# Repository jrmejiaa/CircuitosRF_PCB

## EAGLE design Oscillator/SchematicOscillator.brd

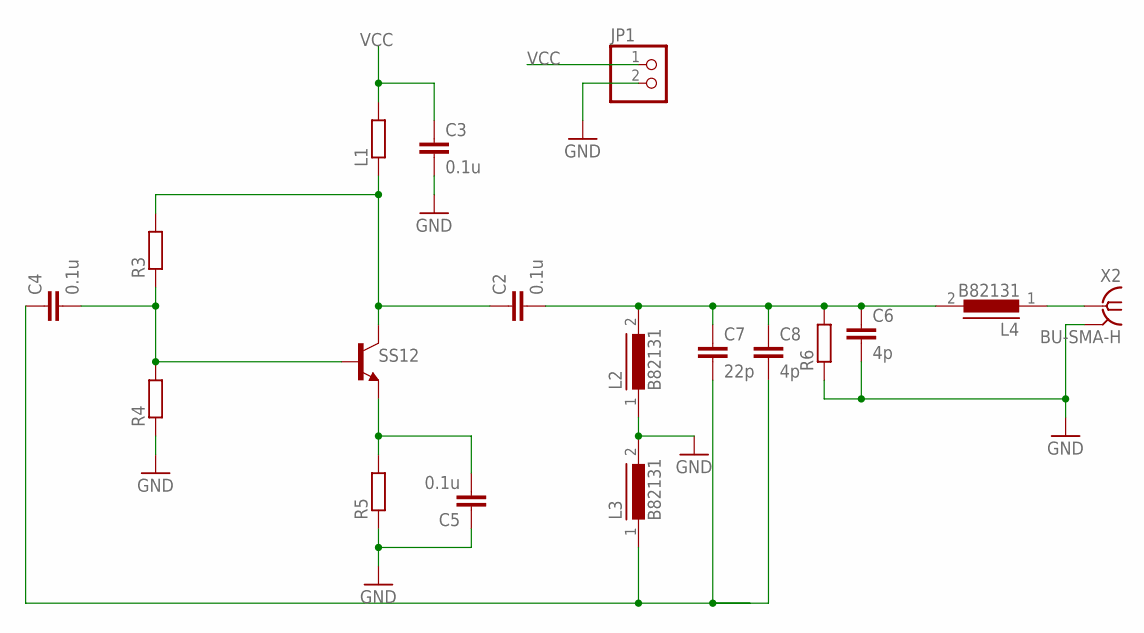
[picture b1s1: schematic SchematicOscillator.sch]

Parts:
C2, C3, C4, C5: 0.1u; C0805
C6, C8: 4p; C1206
C7: 22p; C0805
JP1: PINHD-1X2; 1X02
L1: R-EU_M0805; M0805
L2, L3, L4: B82131; SUKW1-17
R3, R4, R5, R6: R-EU_R1206; R1206
SS12: -NPN-TO92; TO92
X2: BU-SMA-H

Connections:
GND: C3.2, C5.1, C6.2, JP1.2, L2.1, L3.2, R4.1, R5.1, R6.1, X2.2, X2.3 (2), X2.4 (2), X2.5 (2)
unnamed: C2.1, L1.1, R3.2, SS12.3 (C)
unnamed: C5.2, R5.2, SS12.1 (E)
unnamed: C4.2, R3.1, R4.2, SS12.2 (B)
unnamed: L4.1, X2.1
unnamed: C2.2, C6.1, C7.1, C8.1, L2.2, L4.2, R6.2
unnamed: C4.1, C7.2, C8.2, L3.1
VCC: C3.1, JP1.1, L1.2

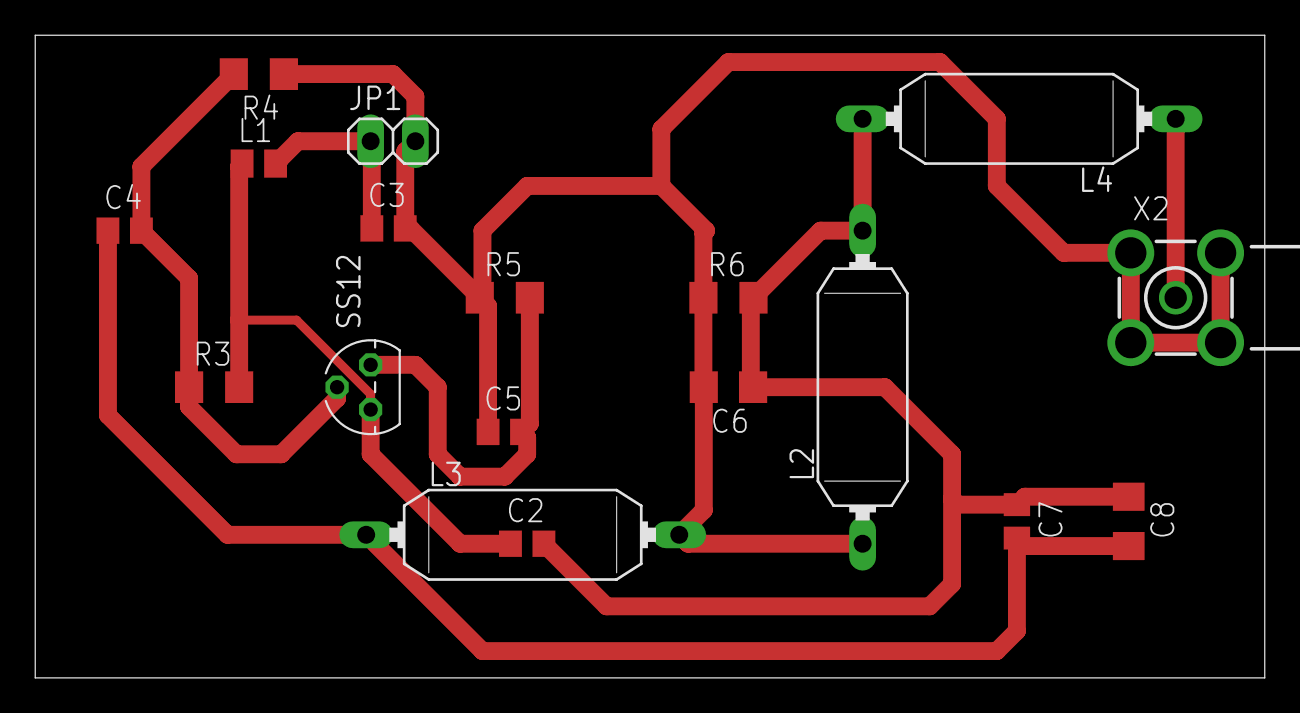
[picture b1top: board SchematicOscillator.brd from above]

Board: 2 copper layers, 69.8 x 36.5 mm, 18 parts (0 on the bottom side), 8 nets.

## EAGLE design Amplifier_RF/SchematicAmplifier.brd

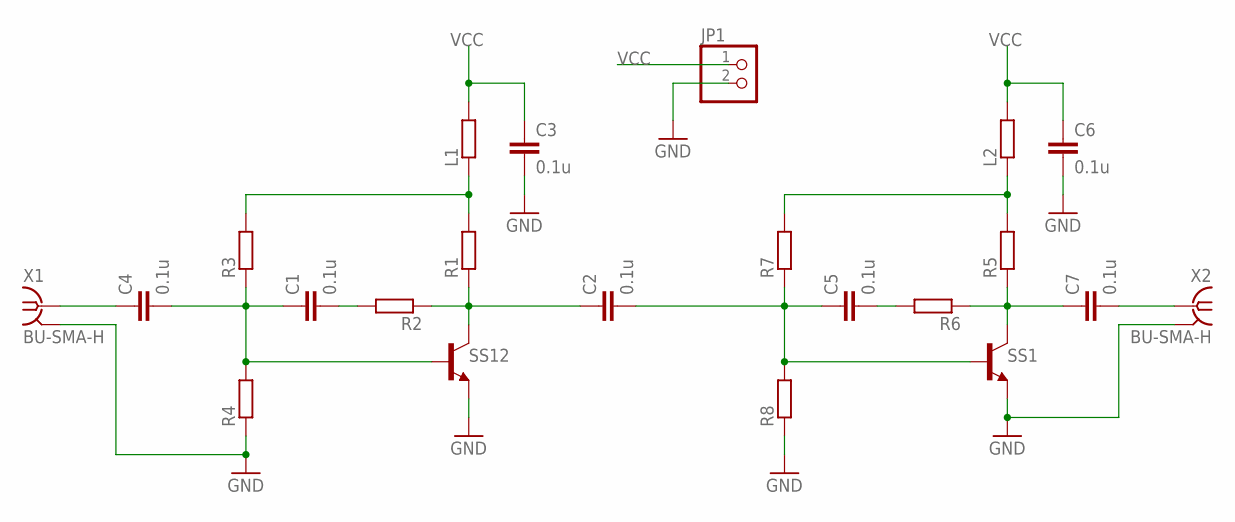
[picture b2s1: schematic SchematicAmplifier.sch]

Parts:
C1, C2, C3, C4, C5, C6, C7: 0.1u; C0805
JP1: PINHD-1X2; 1X02
L1, L2: R-EU_M0805; M0805
R1, R2, R3, R4, R5, R6, R7, R8: R-EU_R1206; R1206
SS1, SS12: -NPN-TO92; TO92
X1, X2: BU-SMA-H

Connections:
GND: C3.2, C6.2, JP1.2, R4.1, R8.1, SS1.1 (E), SS12.1 (E), X1.2, X1.3 (2), X1.4 (2), X1.5 (2), X2.2, X2.3 (2), X2.4 (2), X2.5 (2)
unnamed: C1.2, R2.2
unnamed: L1.1, R1.2, R3.2
unnamed: C2.1, R1.1, R2.1, SS12.3 (C)
unnamed: C4.1, X1.1
unnamed: C1.1, C4.2, R3.1, R4.2, SS12.2 (B)
unnamed: L2.1, R5.2, R7.2
unnamed: C7.1, R5.1, R6.1, SS1.3 (C)
unnamed: C2.2, C5.1, R7.1, R8.2, SS1.2 (B)
unnamed: C5.2, R6.2
unnamed: C7.2, X2.1
VCC: C3.1, C6.1, JP1.1, L1.2, L2.2

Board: 2 copper layers, 22 parts (0 on the bottom side), 12 nets, no tracks yet.

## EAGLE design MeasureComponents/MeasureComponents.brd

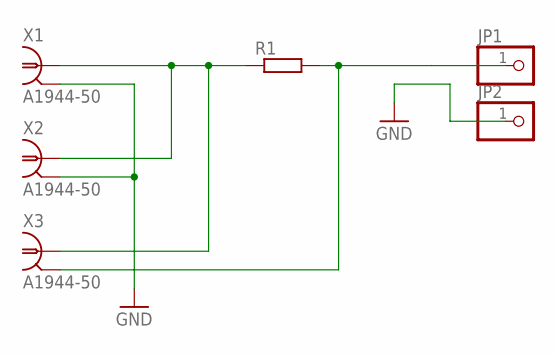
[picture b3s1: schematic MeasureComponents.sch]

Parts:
JP1, JP2: PINHD-1X1; 1X01
R1: R-EU_M1206; M1206
X1, X2, X3: A1944-50; A1944

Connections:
GND: JP2.1, X1.2, X1.3 (2), X1.4 (2), X1.5 (2), X2.2, X2.3 (2), X2.4 (2), X2.5 (2)
unnamed: R1.1, X1.1, X2.1, X3.1
unnamed: JP1.1, R1.2, X3.2, X3.3 (2), X3.4 (2), X3.5 (2)

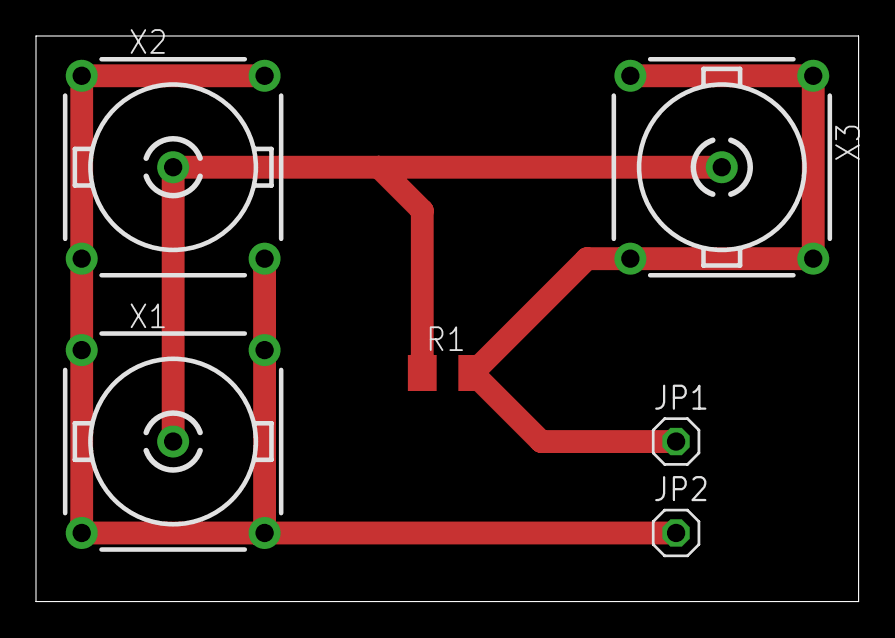
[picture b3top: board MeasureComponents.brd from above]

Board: 2 copper layers, 45.7 x 31.4 mm, 6 parts (0 on the bottom side), 3 nets.

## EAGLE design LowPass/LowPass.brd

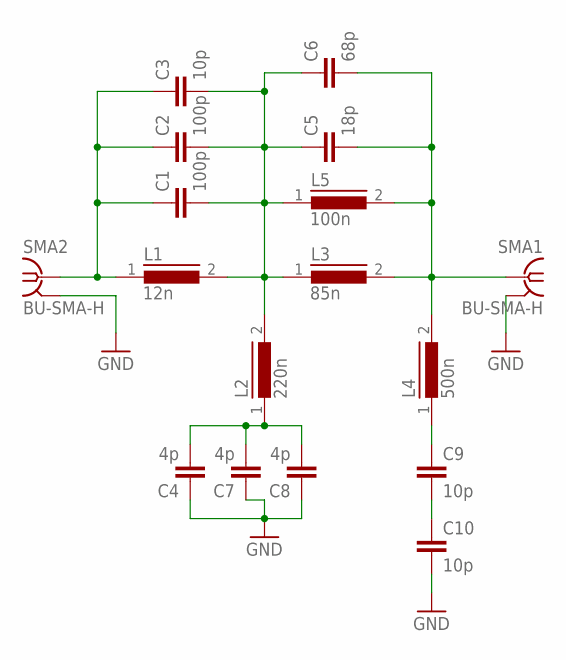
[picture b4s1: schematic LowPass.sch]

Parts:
C1, C2: 100p; C0805
C3, C9, C10: 10p; C0805
C4, C7, C8: 4p; C1206
C5: 18p; C0805
C6: 68p; C0402
L1: 12n; MICC10
L2: 220n; MICC10
L3: 85n; MICC10
L4: 500n; MICC10
L5: 100n; MICC10
SMA1, SMA2: BU-SMA-H

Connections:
GND: C4.1, C7.1, C8.1, C10.2, SMA1.2, SMA1.3 (2), SMA1.4 (2), SMA1.5 (2), SMA2.2, SMA2.3 (2), SMA2.4 (2), SMA2.5 (2)
unnamed: C1.1, C2.1, C3.1, L1.1, SMA2.1
unnamed: C1.2, C2.2, C3.2, C5.1, C6.1, L1.2, L2.2, L3.1, L5.1
unnamed: C5.2, C6.2, L3.2, L4.2, L5.2, SMA1.1
unnamed: C9.1, L4.1
unnamed: C9.2, C10.1
unnamed: C4.2, C7.2, C8.2, L2.1

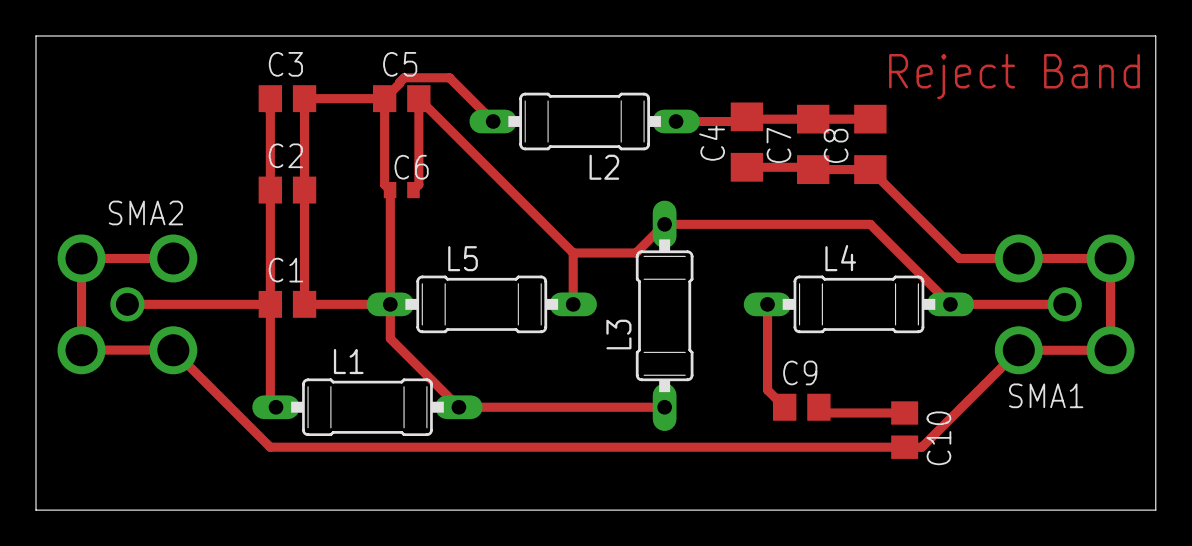
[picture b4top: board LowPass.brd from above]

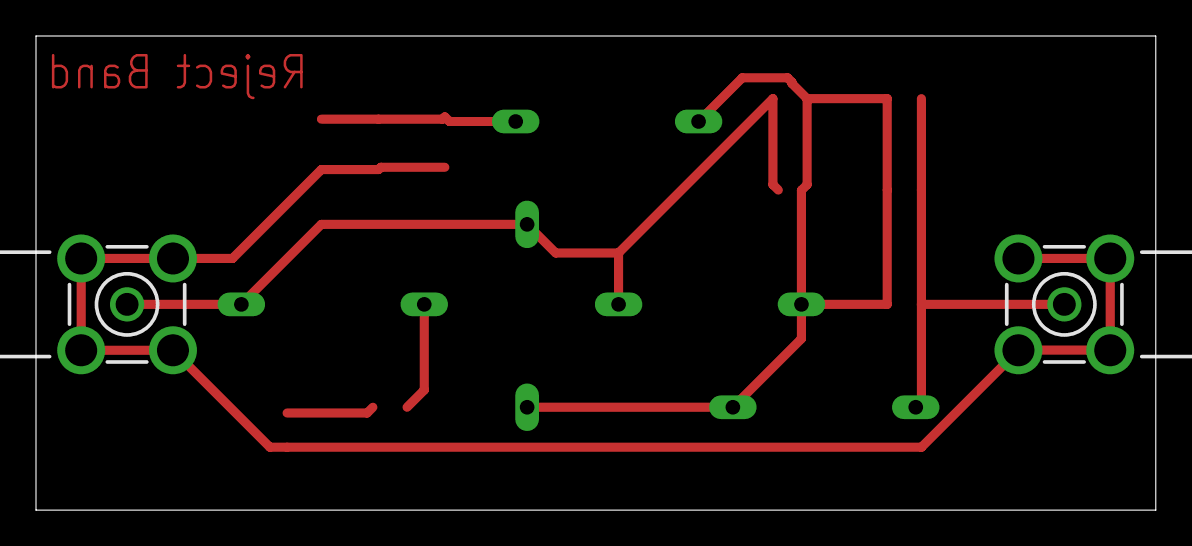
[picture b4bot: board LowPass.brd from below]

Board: 2 copper layers, 62.2 x 26.3 mm, 17 parts (2 on the bottom side), 7 nets.

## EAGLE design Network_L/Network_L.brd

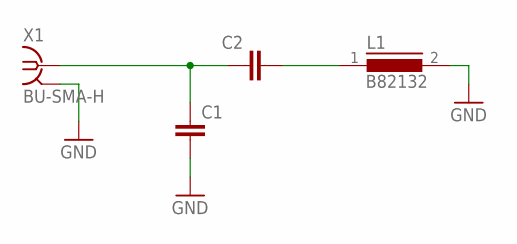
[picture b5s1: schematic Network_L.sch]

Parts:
C1, C2: C-EU075-032X103; C075-032X103
L1: B82132; SUKW2-22
X1: BU-SMA-H

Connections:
GND: C1.2, L1.2, X1.2, X1.3 (2), X1.4 (2), X1.5 (2)
unnamed: C1.1, C2.1, X1.1
unnamed: C2.2, L1.1

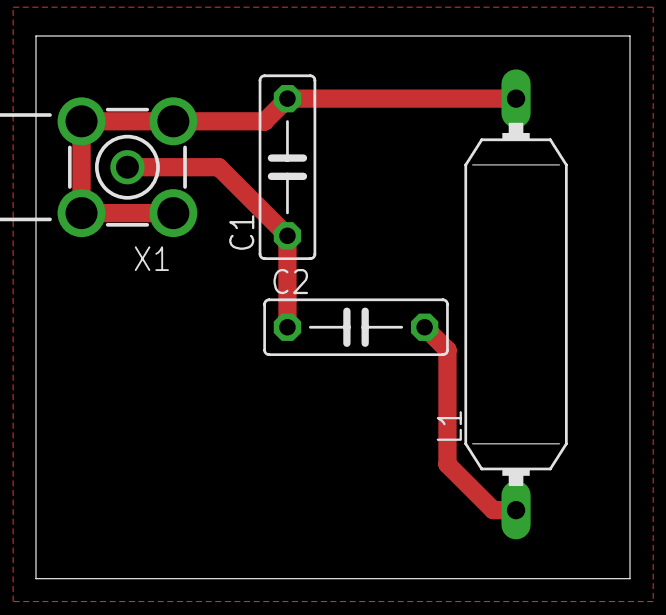
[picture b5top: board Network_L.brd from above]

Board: 2 copper layers, 33.0 x 30.1 mm, 4 parts (0 on the bottom side), 3 nets.

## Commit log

2019-04-19 First PCB design network L
2019-04-19 Gerber files and small change PCB Design
2019-04-29 LowPass and BandStop filter
2019-04-29 Update PCB
2019-05-01 PCB Diseñado
2019-05-01 Copies PCB
2019-05-07 Version SMD Reject Band
2019-05-14 Measure Components - 3 Practica
2019-05-14 Multiple Measure Components PCB
2019-05-26 Amplifier_RF con PDF
2019-05-26 Multiple Amplifier
2019-06-16 Ocillator File - PCB
